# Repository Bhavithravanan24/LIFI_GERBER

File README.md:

# LIFI_GERBER
here the gerber file of my project's pcb and also schematics and other files will be available

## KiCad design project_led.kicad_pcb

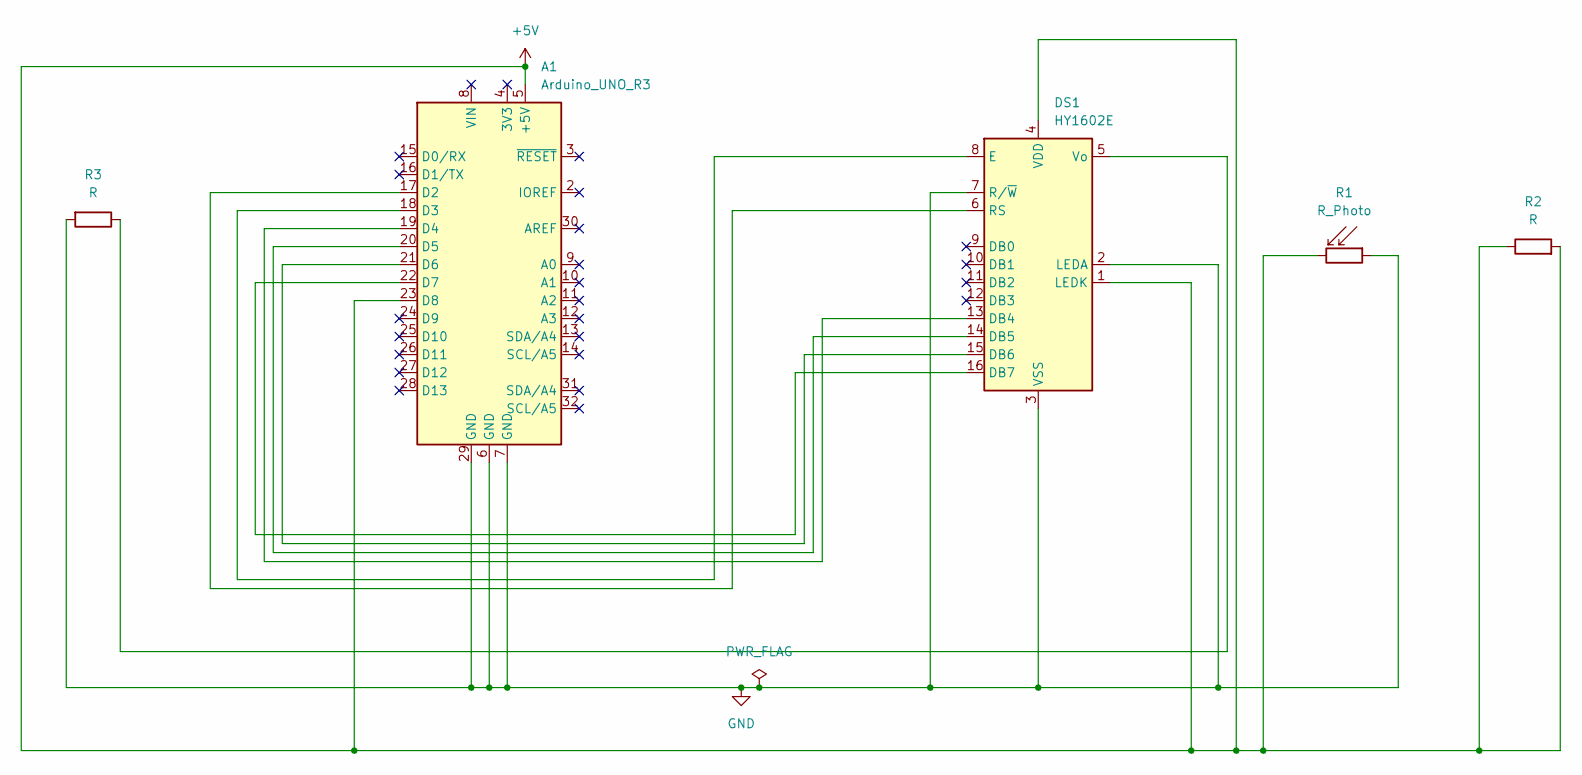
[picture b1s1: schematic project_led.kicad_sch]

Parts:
A1: Arduino_UNO_R3
DS1: HY1602E
R1: R_Photo; R_LDR_D20mm_P17.5mm_Vertical
R2, R3: R; R_0805_2012Metric_Pad1.20x1.40mm_HandSolder

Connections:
+5V: A1.5 (+5V), A1.23 (D8), DS1.1 (LEDK), DS1.4 (VDD), R1.2, R2.1, R2.2
GND: A1.6 (GND), A1.7 (GND), A1.29 (GND), DS1.2 (LEDA), DS1.3 (VSS), DS1.7 (R/~W), R1.1, R3.2
unnamed: A1.17 (D2), DS1.6 (RS)
unnamed: A1.18 (D3), DS1.8 (E)
unnamed: A1.19 (D4), DS1.13 (DB4)
unnamed: A1.20 (D5), DS1.14 (DB5)
unnamed: A1.21 (D6), DS1.15 (DB6)
unnamed: A1.22 (D7), DS1.16 (DB7)
unnamed: DS1.5 (Vo), R3.1

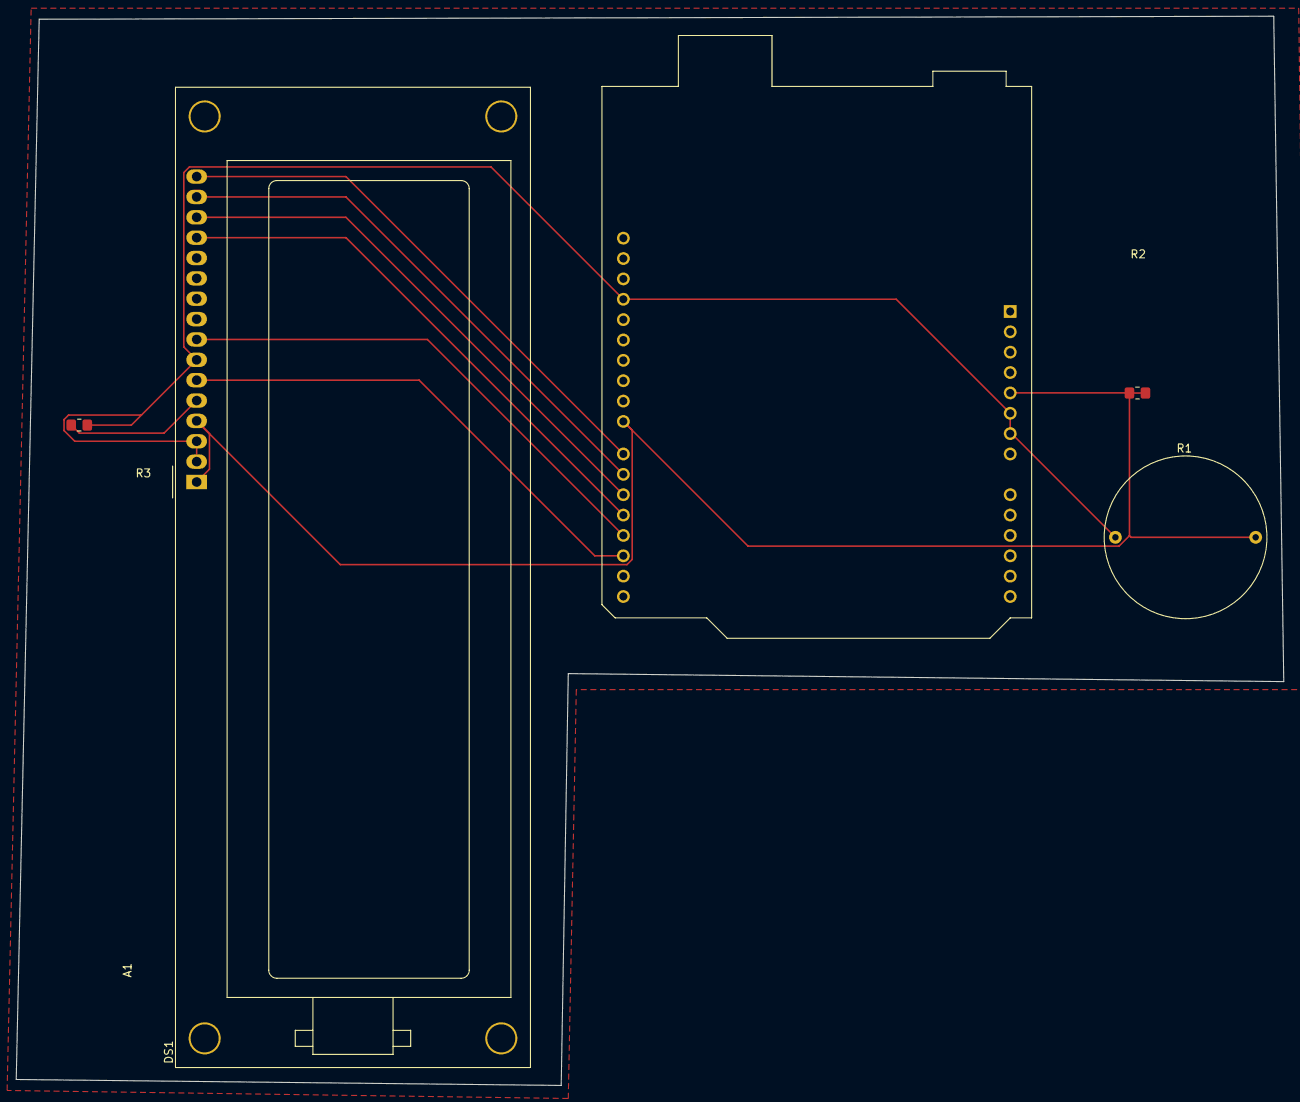
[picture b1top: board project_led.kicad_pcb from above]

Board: 2 copper layers, 158.1 x 133.4 mm, 5 parts (0 on the bottom side), 9 nets.
